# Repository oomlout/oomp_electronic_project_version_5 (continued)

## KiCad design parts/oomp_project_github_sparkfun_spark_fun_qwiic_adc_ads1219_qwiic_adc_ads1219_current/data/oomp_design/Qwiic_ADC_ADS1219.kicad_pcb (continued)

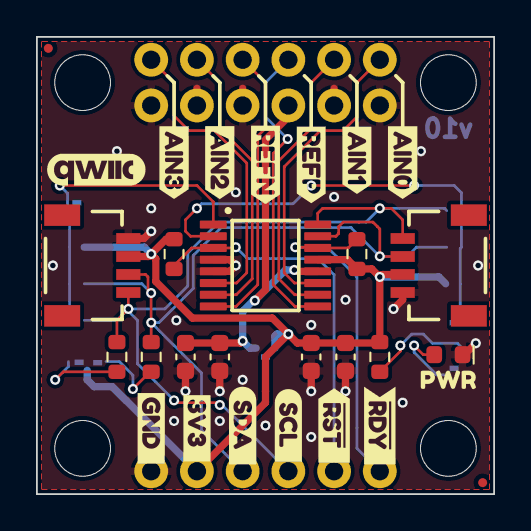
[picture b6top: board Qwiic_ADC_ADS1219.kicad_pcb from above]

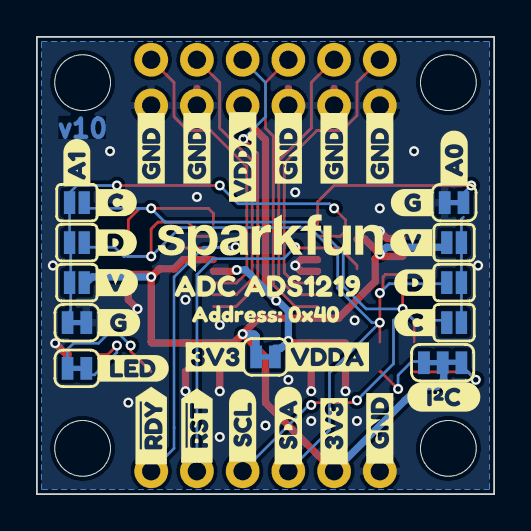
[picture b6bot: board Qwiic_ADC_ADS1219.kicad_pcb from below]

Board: 2 copper layers, 25.4 x 25.4 mm, 75 parts (39 on the bottom side), 19 nets.

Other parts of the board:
kibuzzard-64C3B30F: G***; kibuzzard-64C3B30F
kibuzzard-64C3BD7A: G***; kibuzzard-64C3BD7A
kibuzzard-64C36D1A: G***; kibuzzard-64C36D1A
kibuzzard-64C36D2D: G***; kibuzzard-64C36D2D
kibuzzard-64C36D5B: G***; kibuzzard-64C36D5B
kibuzzard-64C36D6C: G***; kibuzzard-64C36D6C
kibuzzard-64C36D47: G***; kibuzzard-64C36D47
kibuzzard-64C36D91: G***; kibuzzard-64C36D91
kibuzzard-64C37A88: G***; kibuzzard-64C37A88
kibuzzard-64C37CC9: G***; kibuzzard-64C37CC9
kibuzzard-64C38090: G***; kibuzzard-64C38090
kibuzzard-67BCC03F: G***; kibuzzard-67BCC03F
kibuzzard-67BCE7E0: G***; kibuzzard-67BCE7E0
kibuzzard-67BCE9A5: G***; kibuzzard-67BCE9A5
kibuzzard-67BCE9C9: G***; kibuzzard-67BCE9C9
kibuzzard-67BCE9CD: G***; kibuzzard-67BCE9CD
kibuzzard-67BCE9E1: G***; kibuzzard-67BCE9E1
kibuzzard-67BCE80E: G***; kibuzzard-67BCE80E
kibuzzard-67BCE89D: G***; kibuzzard-67BCE89D
kibuzzard-67BCE805: G***; kibuzzard-67BCE805
kibuzzard-67BCE809: G***; kibuzzard-67BCE809
kibuzzard-67BCE889: G***; kibuzzard-67BCE889
kibuzzard-67BCE896: G***; kibuzzard-67BCE896
kibuzzard-67BCE899: G***; kibuzzard-67BCE899
kibuzzard-67BCEA1E: G***; kibuzzard-67BCEA1E
kibuzzard-67BCEA3A: G***; kibuzzard-67BCEA3A
kibuzzard-67BCEA31: G***; kibuzzard-67BCEA31
kibuzzard-67BCEA48: G***; kibuzzard-67BCEA48
kibuzzard-67BCEA55: G***; kibuzzard-67BCEA55
kibuzzard-67BCEA65: G***; kibuzzard-67BCEA65
kibuzzard-67BCEA70: G***; kibuzzard-67BCEA70
kibuzzard-67BCEAAB: G***; kibuzzard-67BCEAAB
kibuzzard-67BCEAC6, kibuzzard-67BCEAC6#2, kibuzzard-67BCEAC6#3, kibuzzard-67BCEAC6#4, kibuzzard-67BCEAC6#5: G***; kibuzzard-67BCEAC6
kibuzzard-67BCEAE1: G***; kibuzzard-67BCEAE1
kibuzzard-67BCEB1D: G***; kibuzzard-67BCEB1D
kibuzzard-67BCEB15: G***; kibuzzard-67BCEB15
kibuzzard-67BCEB32: G***; kibuzzard-67BCEB32

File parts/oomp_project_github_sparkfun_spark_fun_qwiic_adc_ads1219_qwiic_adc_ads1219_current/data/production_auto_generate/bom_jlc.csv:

Comment,Designator,Footprint,LCSC Part #
0.1uF,"C2,C4",SparkFun-Capacitor:C_0603_1608Metric,C14663
10k,"R4,R5",SparkFun-Resistor:R_0603_1608Metric,C98220
1k,R1,SparkFun-Resistor:R_0603_1608Metric,C2907002
2.2k,"R2,R3",SparkFun-Resistor:R_0603_1608Metric,C4190
2.2uF,"C1,C3",SparkFun-Capacitor:C_0603_1608Metric,C23630
ADS1219IPW,U1,SparkFun-Semiconductor-Standard:TSSOP-16,
C,"JP7,JP11",SparkFun-Jumper:Jumper_2_NO,
Conn_01x02,J5,SparkFun-Connector:1x02,C492401
Conn_01x06,"J3,J4",SparkFun-Connector:1x06,C37208
D,"JP6,JP10",SparkFun-Jumper:Jumper_2_NO,
G,"JP4,JP8",SparkFun-Jumper:Jumper_2_NC_Trace,
I2C,J6,SparkFun-Connector:1x04,C42431795
Qwiic_RA,"J1,J2",SparkFun-Connector:JST_SMD_1.0mm-4_Black,C160404
Red,D1,SparkFun-LED:LED_0603_1608Metric_Red,
V,"JP5,JP9",SparkFun-Jumper:Jumper_2_NO,
~,"JP1,JP2",SparkFun-Jumper:Jumper_2_NC_Trace,
~,JP3,SparkFun-Jumper:Jumper_3_NC-2_Trace,

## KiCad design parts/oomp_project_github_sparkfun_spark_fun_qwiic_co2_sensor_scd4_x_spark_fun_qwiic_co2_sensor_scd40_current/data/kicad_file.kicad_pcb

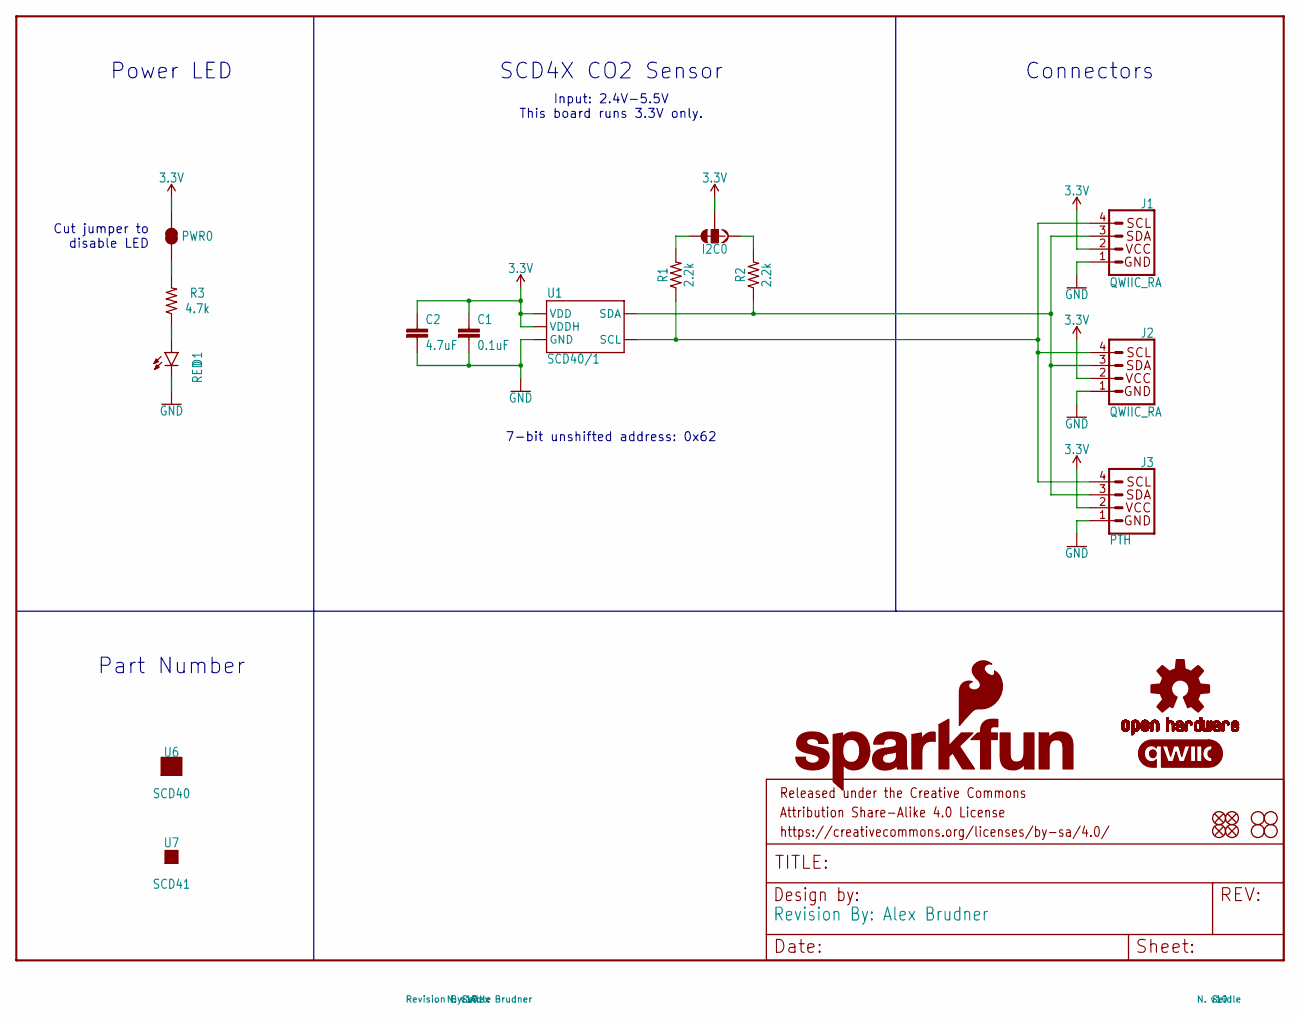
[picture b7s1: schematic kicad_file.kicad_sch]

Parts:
C1: 0.1uF; 0603
C2: 4.7uF; 0603
D1: RED; LED-0603
FD1, FD2, FD3, FD4: FIDUCIALUFIDUCIAL; FIDUCIAL-MICRO
FRAME1: FRAME-LETTER; CREATIVE_COMMONS
H1, H2, H3, H4: STAND-OFF
I2C0: I2C; SMT-JUMPER_3_2-NC_TRACE_SILK
J1, J2: QWIIC_RA; JST04_1MM_RA
J3: PTH; 1X04_NO_SILK
LOGO1: QWIIC_LOGO_CONNECTOR; QWIIC_5.5MM
LOGO2: OSHW-LOGOS; OSHW-LOGO-S
LOGO3: SFE_LOGO_NAME_FLAMEBLANK; BLANK
PWR0: PWR; SMT-JUMPER_2_NC_TRACE_SILK
R1, R2: 2.2k; 0603
R3: 4.7k; 0603
U1: SCD40/1; SCD4X
U6: SCD40; PRODUCT_IDENT_PASTE_NO-SILK
U7: SCD41; PRODUCT_IDENT_NO_NO-SILK

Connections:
3.3V: C1.1, C2.1, I2C0.2, J1.2, J2.2, J3.2, PWR0.2, U1.7 (VDD), U1.19 (VDDH)
GND: C1.2, C2.2, D1.C, J1.1, J2.1, J3.1, U1.6 (GND), U1.20 (GND), U1.CP (GND)
unnamed: I2C0.1, R2.2
unnamed: I2C0.3, R1.2
unnamed: PWR0.1, R3.2
unnamed: D1.A, R3.1
SCL: J1.4, J2.4, J3.4, R1.1, U1.9 (SCL)
SDA: J1.3, J2.3, J3.3, R2.1, U1.10 (SDA)

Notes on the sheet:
SCD4X CO2 Sensor
7-bit unshifted address: 0x62
Input: 2.4V-5.5V This board runs 3.3V only.
Power LED
Cut jumper to disable LED
Connectors
Part Number

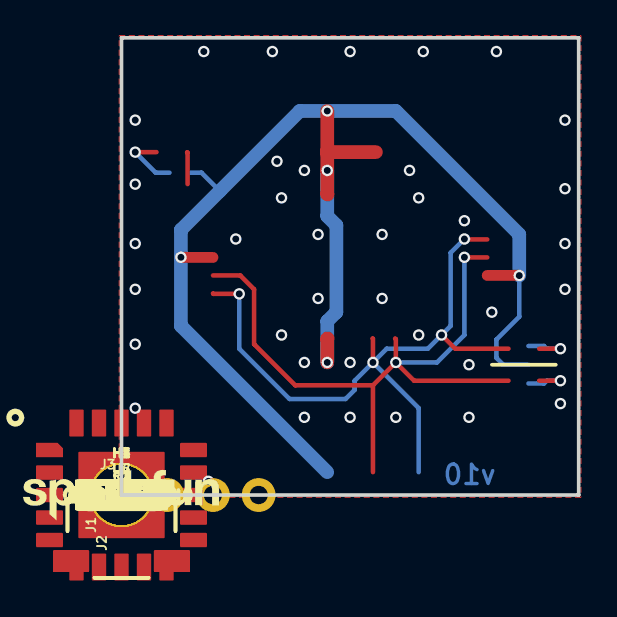
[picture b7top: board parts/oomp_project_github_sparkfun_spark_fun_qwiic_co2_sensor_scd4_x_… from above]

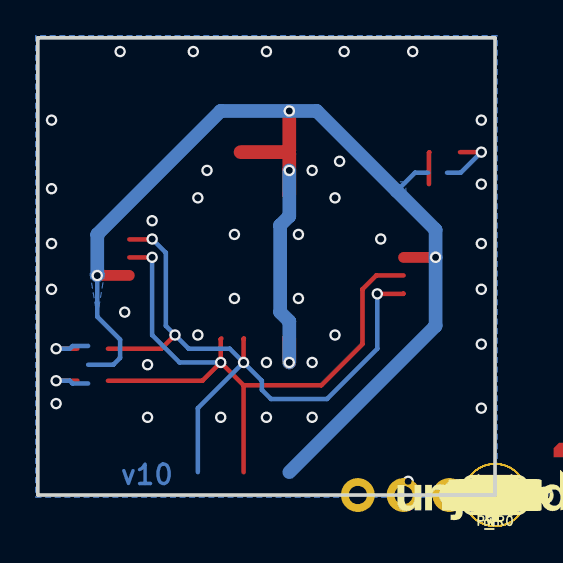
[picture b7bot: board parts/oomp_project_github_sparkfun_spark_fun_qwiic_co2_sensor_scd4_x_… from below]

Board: 2 copper layers, 25.4 x 25.4 mm, 49 parts (16 on the bottom side), 8 nets.

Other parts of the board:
U$1, U$18: #_GND#14
U$2, U$19: #_3V3#15
U$3, U$20: #_SDA#15
U$4, U$21: #_SCL#16
U$5, U$12: SFE_LOGO_NAME_.1
U$6: SCD414140404021
U$7: SCD40414140404022
U$8, U$13: QWIIC_CO0
U$9, U$14: SENSOR0
U$10, U$15: 20
U$11: SFE_LOGO_FLAME_STOP_.1
U$16: #PLED#21
U$17: #I�C#0
U$22: ORDERING_INSTRUCTIONS
U$23: PWR0
